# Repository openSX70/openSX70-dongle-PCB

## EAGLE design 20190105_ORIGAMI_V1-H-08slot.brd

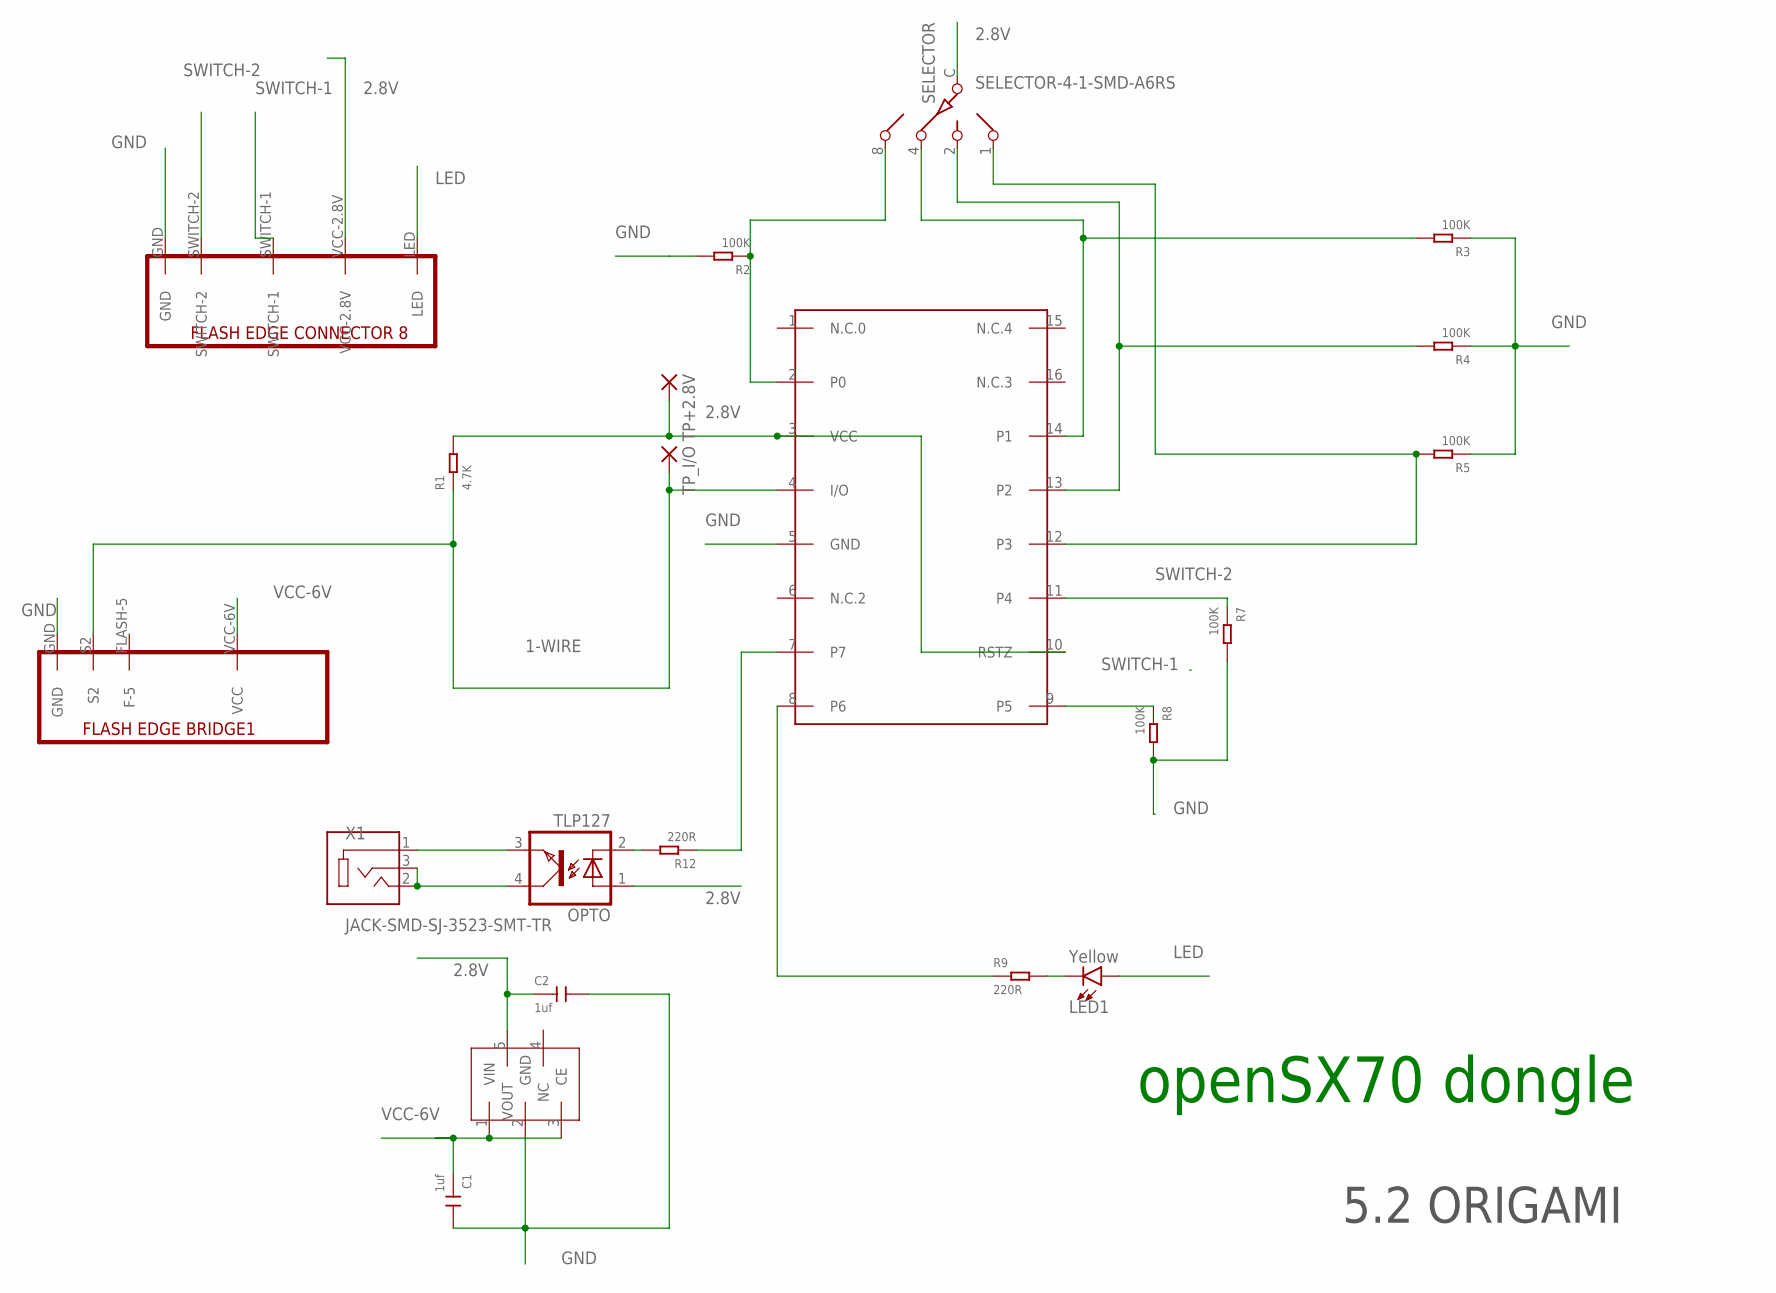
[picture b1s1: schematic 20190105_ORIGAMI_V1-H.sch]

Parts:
C1, C2: 1uf; C0603
DS2408: DS2408; SO16
LED1: Yellow; LED-1206
OPTO: TLP127; SO-4
R1: 4.7K; R0603
R2, R3, R4, R5, R7, R8: 100K; R0603
R9, R12: 220R; R0603
REG: NCP4688; SOT-23-5
SELECTOR: SELECTOR-4-1-SMD-A6RS; A6RS-161RS
TP+2.8V: SMD2; SMD1,27-2,54
TP_I/O: SMD2; SMD1,27-2,54
U$1: FLASH-BRIDGE-SW1-SW2-LED; FLASH-8-BRIDGE-SW1-SW2-LED
U$2: FLASH-BRIDGE1; FLASH-8-BRIDGE1
X1: JACK-SMD-SJ-3523-SMT-TR; CUI_SJ-3523-SMT-TR

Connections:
1-WIRE: DS2408.4 (I/O), R1.1, TP_I/O.1, U$2.S2
2.8V: C2.1, DS2408.3 (VCC), DS2408.10 (RSTZ), OPTO.1 (A), R1.2, REG.5 (VOUT), SELECTOR.C, TP+2.8V.1, U$1.VCC-2.8V
GND: C1.2, C2.2, DS2408.5 (GND), R2.2, R3.1, R4.1, R5.1, R7.2, R8.2, REG.2 (GND), U$1.GND, U$2.GND
LED: LED1.A, U$1.LED
unnamed: OPTO.3 (EMIT), X1.1
unnamed: LED1.C, R9.2
unnamed: DS2408.2 (P0), R2.1, SELECTOR.8
unnamed: DS2408.14 (P1), R3.2, SELECTOR.4
unnamed: DS2408.13 (P2), R4.2, SELECTOR.2
unnamed: DS2408.8 (P6), R9.1
unnamed: OPTO.4 (COL), X1.2, X1.3
unnamed: OPTO.2 (C), R12.2
unnamed: DS2408.7, R12.1
unnamed: DS2408.12 (P3), R5.2, SELECTOR.1
SWITCH-1: DS2408.9 (P5), R8.1, U$1.SWITCH-1
SWITCH-2: DS2408.11 (P4), R7.1, U$1.SWITCH-2
VCC-6V: C1.1, REG.1 (VIN), REG.3 (CE), U$2.VCC-6V (VCC)

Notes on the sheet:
openSX70 dongle
5.2 ORIGAMI

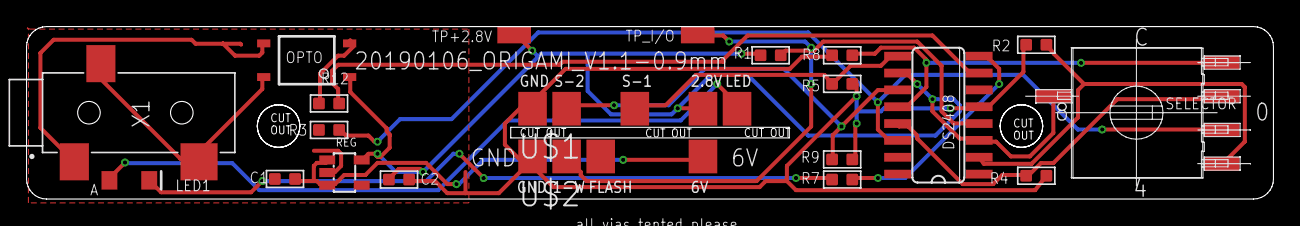
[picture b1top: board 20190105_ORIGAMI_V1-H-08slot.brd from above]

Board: 2 copper layers, 94.0 x 13.0 mm, 21 parts (0 on the bottom side), 17 nets.

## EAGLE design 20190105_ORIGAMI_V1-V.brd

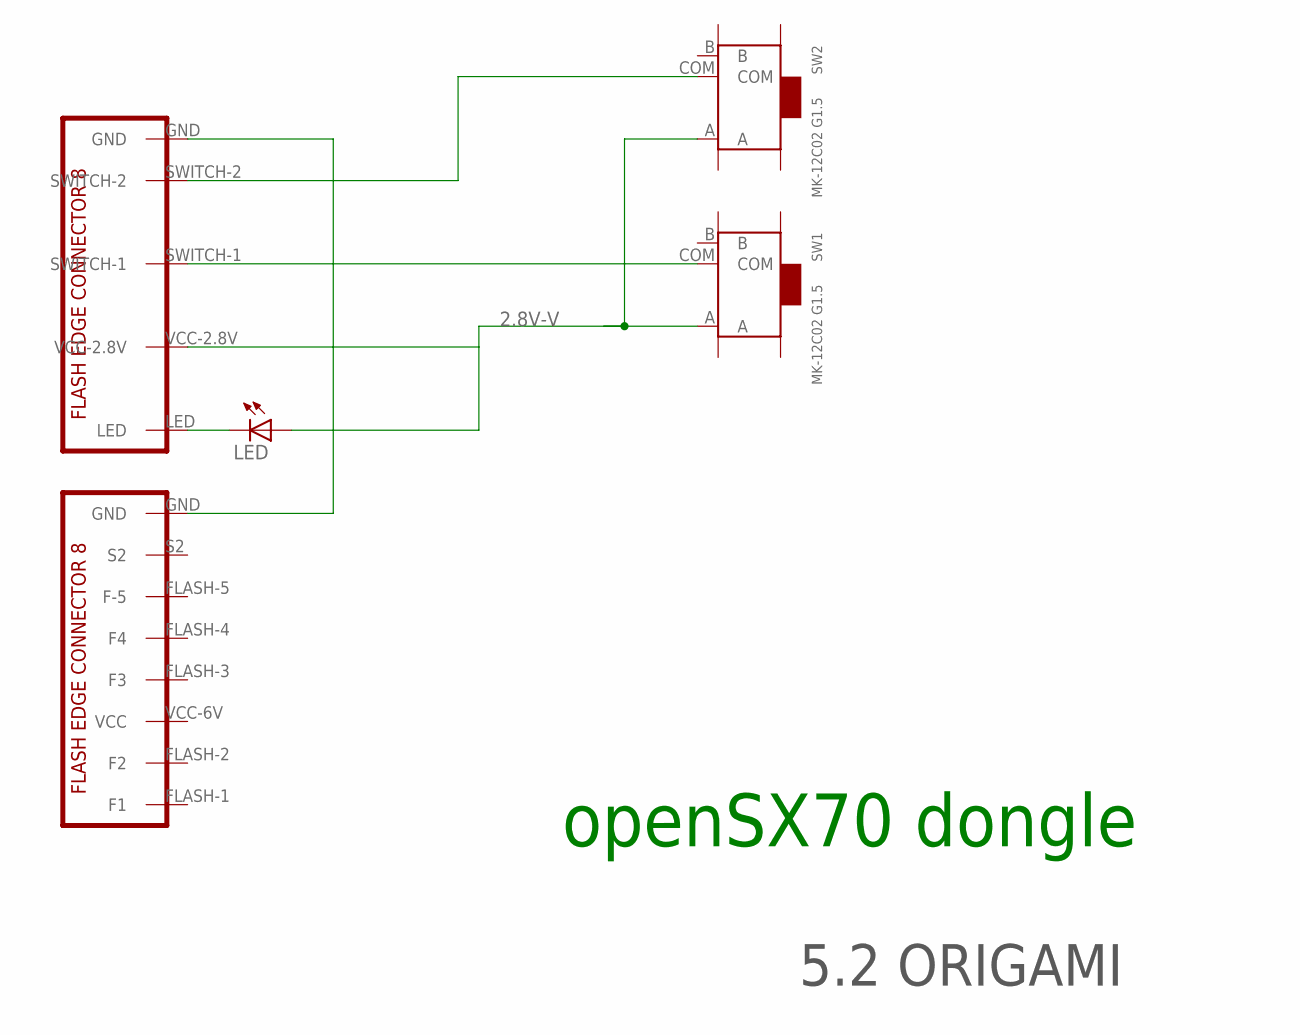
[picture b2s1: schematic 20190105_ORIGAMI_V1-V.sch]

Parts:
LED: LEDCHIP-LED0805; CHIP-LED0805
SW1, SW2: MK-12C02 G1.5; SW7-SMD-L6.7X2.7X3.2MM
U$1: FLASH-BRIDGE-SW1-SW2-LED-SMALL; FLASH-8-BRIDGE-SW1-SW2-LED-SMALL
U$2: SX70-FLASH-EDGE8-MALE-LONG; SX70-FLASH-EDGE8-2

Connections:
2.8V-V: LED.A, SW1.A, SW2.A, U$1.VCC-2.8V
unnamed: U$1.GND, U$2.GND
unnamed: SW1.COM, U$1.SWITCH-1
unnamed: SW2.COM, U$1.SWITCH-2
unnamed: LED.C, U$1.LED

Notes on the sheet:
openSX70 dongle
5.2 ORIGAMI

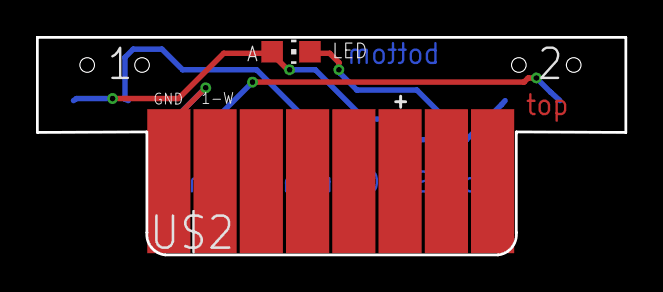
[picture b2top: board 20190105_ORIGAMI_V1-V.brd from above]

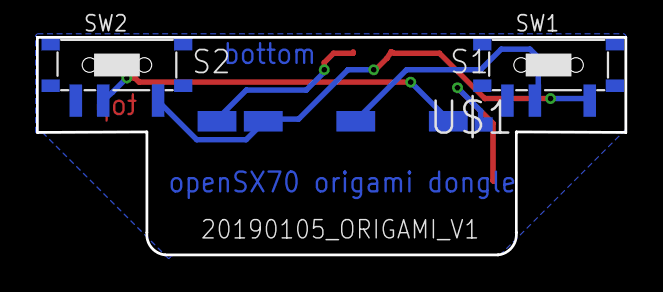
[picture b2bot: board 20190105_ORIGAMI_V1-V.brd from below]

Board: 2 copper layers, 32.7 x 12.1 mm, 5 parts (3 on the bottom side), 5 nets.

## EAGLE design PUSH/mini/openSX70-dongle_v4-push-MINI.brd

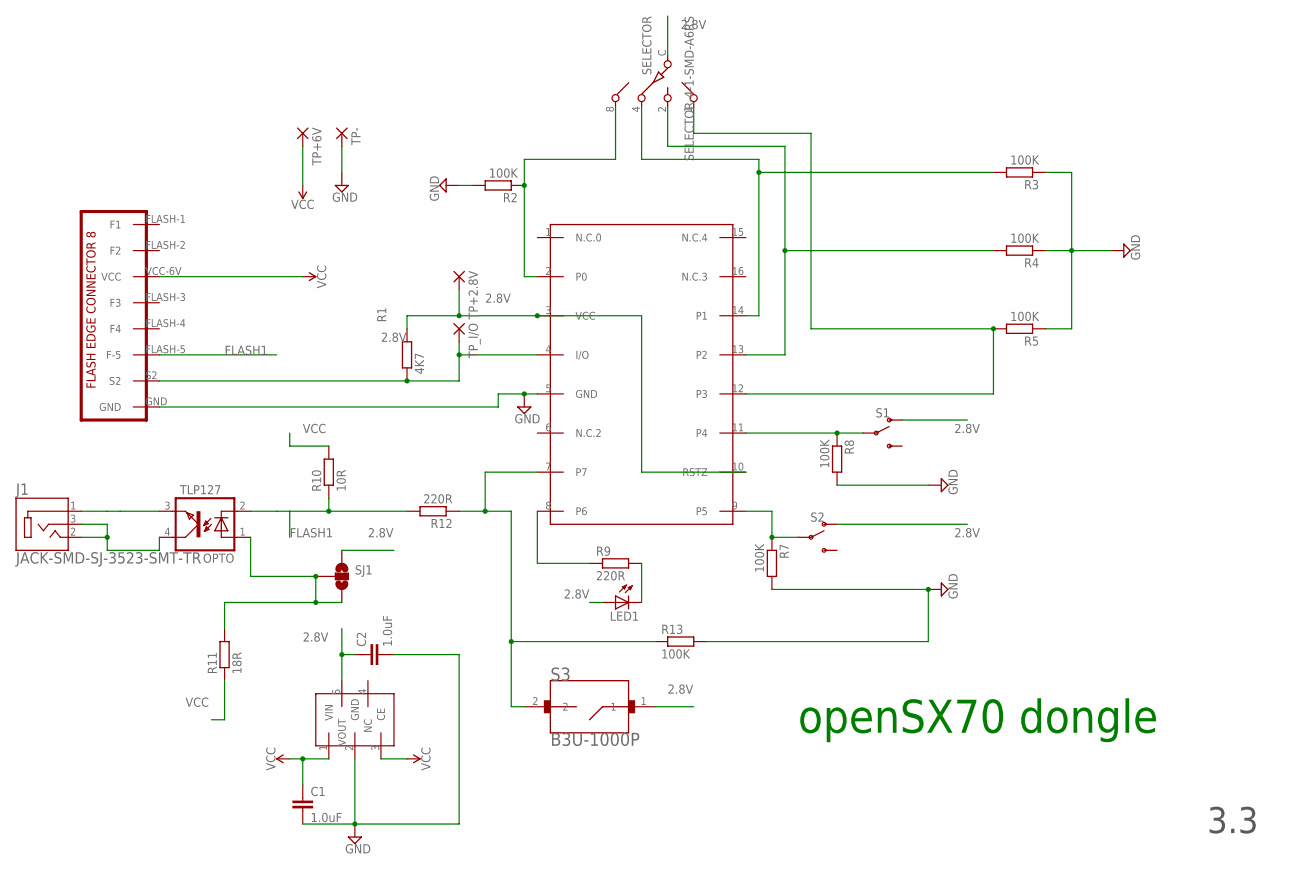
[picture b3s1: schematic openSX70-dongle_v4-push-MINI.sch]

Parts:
C1, C2: 1.0uF; C0603
DS2408: DS2408; SO16
J1: JACK-SMD-SJ-3523-SMT-TR; CUI_SJ-3523-SMT-TR
LED1: LED3MM
OPTO: TLP127; SO-4
R1: 4K7; R0603
R2, R3, R4, R5, R7, R8, R13: 100K; R0603
R9, R12: 220R; R0603
R10: 10R; R0603
R11: 18R; R0603
REG: NCP4688; SOT-23-5
S1, S2: SWITCH-SPDT-SMD-RIGHT-ANGLE; SWITCH_SPST_SMD_A
S3: B3U-1000P; SW_B3U-1000P
SELECTOR: SELECTOR-4-1-SMD-A6RS; A6RS-161RS
SJ1: SOLDERJUMPER_2WAYS; SJ_3
TP+2.8V, TP+6V: SMD2; SMD1,27-2,54
TP-: SMD2; SMD1,27-2,54
TP_I/O: SMD2; SMD1,27-2,54
U$2: SX70-FLASH-EDGE8-MALE-PROPER; SX70-FLASH-EDGE8

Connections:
2.8V: C2.1, DS2408.3 (VCC), DS2408.10 (RSTZ), LED1.A, R1.2, REG.5 (VOUT), S1.1 (O), S2.1 (O), S3.1, SELECTOR.C, SJ1.1, TP+2.8V.1
FLASH1: OPTO.1 (A), OPTO.2 (C), R10.1, R11.2, R12.2, SJ1.2, SJ1.3, U$2.FLASH-5 (F-5)
GND: C1.2, C2.2, DS2408.5 (GND), R2.2, R3.1, R4.1, R5.1, R7.2, R8.2, R13.2, REG.2 (GND), TP-.1, U$2.GND
unnamed: DS2408.4 (I/O), R1.1, TP_I/O.1, U$2.S2
unnamed: LED1.K (C), R9.2
unnamed: DS2408.2 (P0), R2.1, SELECTOR.8
unnamed: DS2408.14 (P1), R3.2, SELECTOR.4
unnamed: DS2408.13 (P2), R4.2, SELECTOR.2
unnamed: DS2408.11 (P4), R8.1, S1.2
unnamed: DS2408.9 (P5), R7.1, S2.2
unnamed: DS2408.8 (P6), R9.1
unnamed: DS2408.7, R12.1, R13.1, S3.2
unnamed: J1.2, J1.3, OPTO.4 (COL)
unnamed: DS2408.12 (P3), R5.2, SELECTOR.1
unnamed: J1.1, OPTO.3 (EMIT)
VCC: C1.1, R10.2, R11.1, REG.1 (VIN), REG.3 (CE), TP+6V.1, U$2.VCC-6V (VCC)

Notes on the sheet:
openSX70 dongle
3.3

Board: 2 copper layers, 29 parts (3 on the bottom side), 16 nets, no tracks yet.

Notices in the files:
parts and their libraries:
SparkFun-LED: Licensing: Creative Commons ShareAlike 4.0 International - https://creativecommons.org/licenses/by-sa/4.0
SparkFun-Passives: Licensing: CC v3.0 Share-Alike You are welcome to use this library for commercial purposes.
